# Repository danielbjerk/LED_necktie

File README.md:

# LED_necktie

## Components

### Amount of bus-pins
SPI requires 3 pins for SCK, MISO and MOSI. The middle bus is reserved to GND. Since the design should be mirrored, the total amount of pins on the bus is (3 + x)*2 + 1, with x being the amount of pins dedicated to (multiplexing) chip select.

I.e. if 4 pins are dedicated to CHPSLCK (meaning 2^4-1=15 slaves can be selected (since 0 from the demux must be no-connect to allow selecting no slaves (MEN CHIP 0 er alltid MASTER!))) then 15 pins are needed. This exists.

Alternatively: One could use a non-doubled bus and connect to two spi-ports, one being flipped. Then a build flag could define which definition is used.

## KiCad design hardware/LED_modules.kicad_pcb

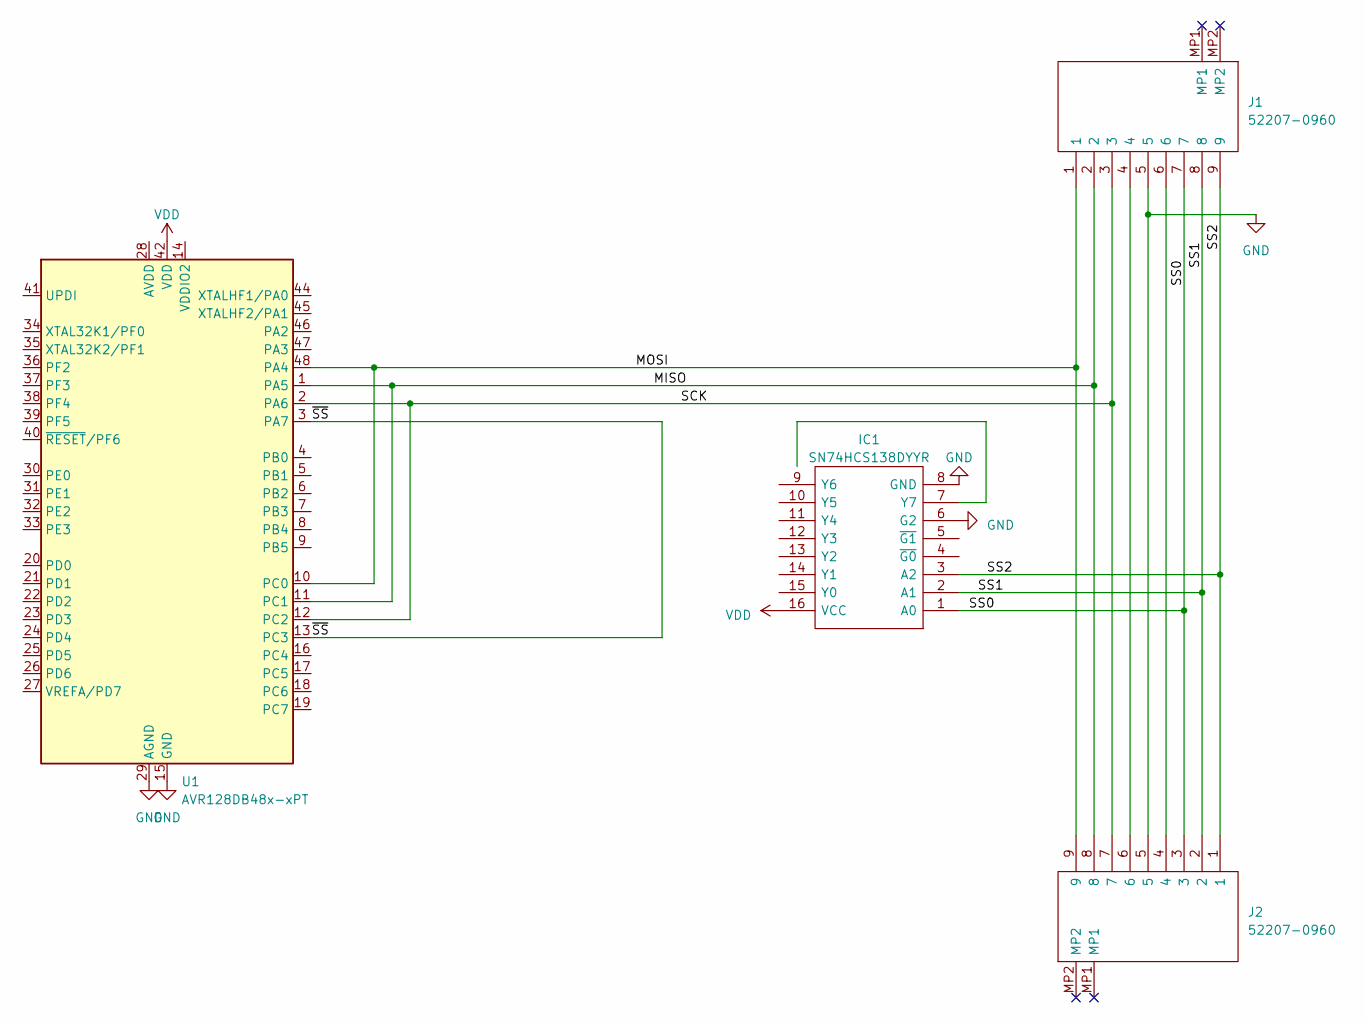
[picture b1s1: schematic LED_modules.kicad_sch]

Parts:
IC1: SN74HCS138DYYR; SOP50P326X110-16N; Mouser Part Number 595-SN74HCS138DYYR
J1, J2: 52207-0960; 522070960; Mouser Part Number 538-52207-0960
U1: AVR128DB48x-xPT; TQFP-48_7x7mm_P0.5mm

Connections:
/MISO: J1.2, J2.8, U1.1 (PA5), U1.11 (PC1)
/MOSI: J1.1, J2.9, U1.10 (PC0), U1.48 (PA4)
/SCK: J1.3, J2.7, U1.2 (PA6), U1.12 (PC2)
/SS0: IC1.1 (A0), J1.7, J2.3
/SS1: IC1.2 (A1), J1.8, J2.2
/SS2: IC1.3 (A2), J1.9, J2.1
/~SS: U1.3 (PA7), U1.13 (PC3)
GND: IC1.6 (G2), IC1.8 (GND), J1.5, J2.5, U1.15 (GND), U1.29 (AGND), U1.43 (GND)
unnamed: J1.4, J2.6
unnamed: J1.6, J2.4
VDD: IC1.16 (VCC), U1.42 (VDD)

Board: 2 copper layers, 4 parts (0 on the bottom side), 11 nets, no tracks yet.

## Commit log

2023-03-03 Create Atmel Studio Project
2023-03-03 Add code skeleton, move files to src and include
2023-03-03 Program compiles, blink
2023-03-03 Complete working master, slave does not correctly read READY-signal
2023-03-06 Complete bad multi-color implementation
2023-03-17 BAD implementation, TOdo: make hardware only header of pins
2023-03-17 Sif fix, funker nå
2023-03-19 Refactoring, move inits to fitting modules, rename hardware to pins
2023-03-31 Begin PCB. Cant find resistor-symbol:-)
